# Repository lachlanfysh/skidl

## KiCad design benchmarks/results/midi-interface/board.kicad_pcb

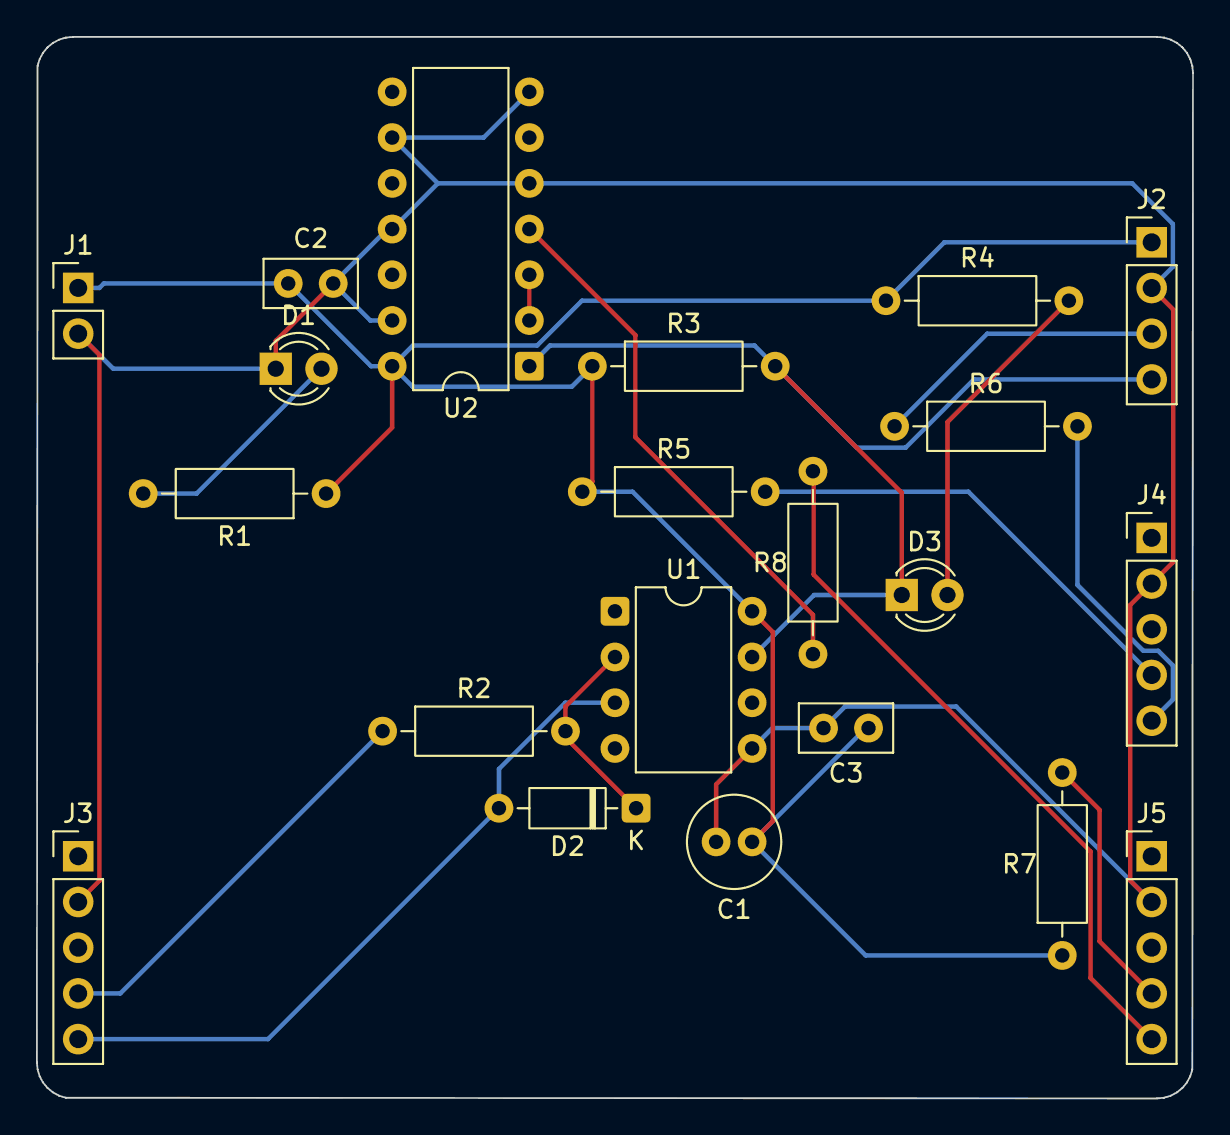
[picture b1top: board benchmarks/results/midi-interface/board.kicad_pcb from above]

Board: 2 copper layers, 64.2 x 59.0 mm, 21 parts (0 on the bottom side), 15 nets.

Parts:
C1: 10uF; C_Radial_D5.0mm_H11.0mm_P2.00mm
C2, C3: 100nF; C_Disc_D5.0mm_W2.5mm_P2.50mm
D1: GREEN; LED_D3.0mm
D2: 1N4148; D_DO-35_SOD27_P7.62mm_Horizontal
D3: YELLOW; LED_D3.0mm
J1: 5V PWR; PinHeader_1x02_P2.54mm_Vertical
J2: MCU HDR; PinHeader_1x04_P2.54mm_Vertical
J3: MIDI IN; PinHeader_1x05_P2.54mm_Vertical
J4: MIDI OUT; PinHeader_1x05_P2.54mm_Vertical
J5: MIDI THRU; PinHeader_1x05_P2.54mm_Vertical
R1, R4: 470; R_Axial_DIN0207_L6.3mm_D2.5mm_P10.16mm_Horizontal
R2, R5, R6, R7, R8: 220; R_Axial_DIN0207_L6.3mm_D2.5mm_P10.16mm_Horizontal
R3: 4.7k; R_Axial_DIN0207_L6.3mm_D2.5mm_P10.16mm_Horizontal
U1: 6N138; DIP-8_W7.62mm
U2: 74HC14; DIP-14_W7.62mm

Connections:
GND: C1.2, C2.2, C3.2, D1.1, J1.2, J2.2, J3.2, J4.2, J5.2, U1.5, U2.5, U2.7, U2.9, U2.11, U2.13
MIDI_IN_RAW: D3.1, J2.4, R3.2, U1.7, U2.1
MIDI_OUT_TX: J2.3, R6.1
MIDI_THRU_BUF: R8.1, U2.4
MID_INV: U2.2, U2.3
unnamed: D1.2, R1.2
unnamed: J3.4, R2.1
unnamed: D3.2, R4.2
unnamed: J4.4, R5.2
unnamed: J4.5, R6.2
unnamed: J5.4, R7.2
unnamed: J5.5, R8.2
OPTO_A: D2.1, R2.2, U1.2
OPTO_C: D2.2, J3.5, U1.3
VCC: C1.1, C2.1, C3.1, J1.1, J2.1, R1.1, R3.1, R4.1, R5.1, R7.1, U1.8, U2.14

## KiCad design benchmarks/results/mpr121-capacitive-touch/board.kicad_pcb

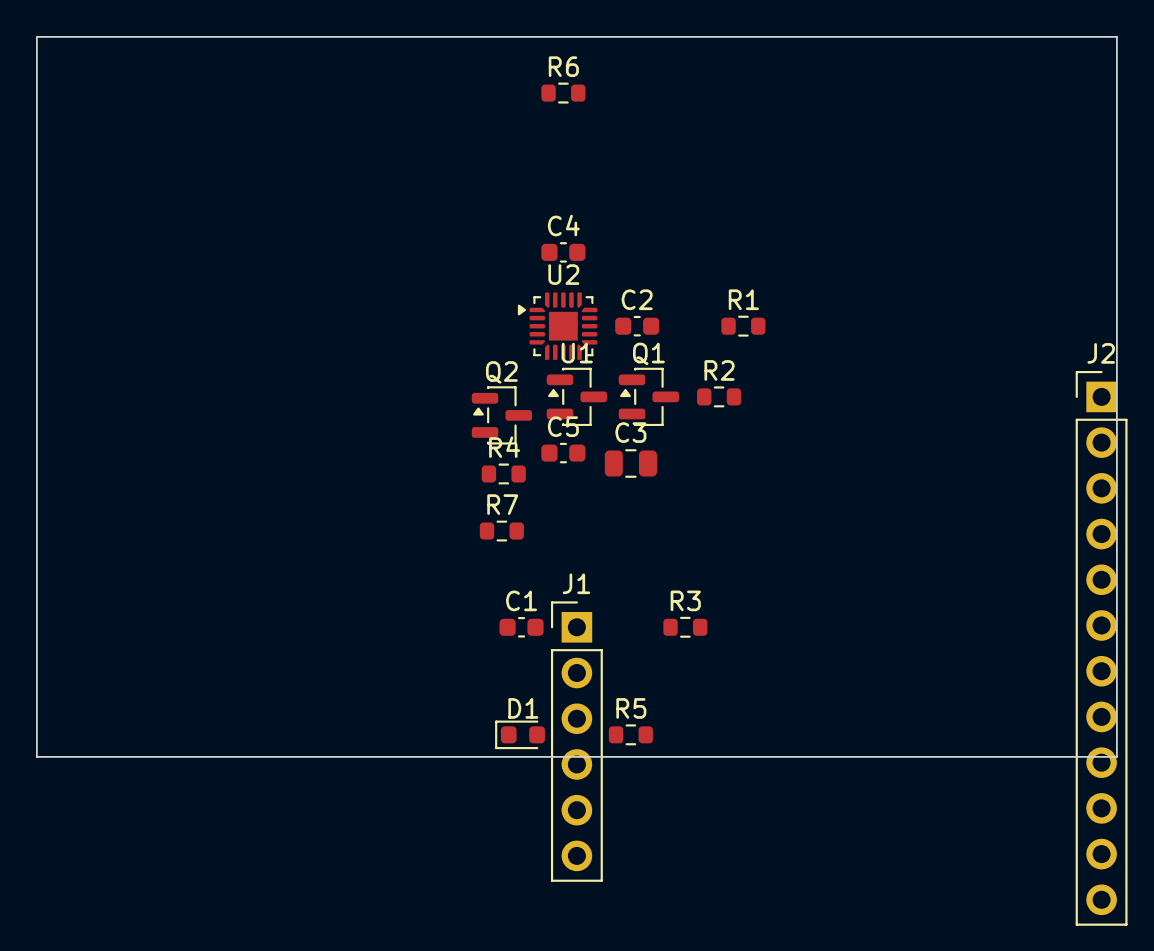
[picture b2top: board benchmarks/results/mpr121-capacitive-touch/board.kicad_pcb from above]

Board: 2 copper layers, 60.0 x 40.0 mm, 19 parts (0 on the bottom side), 23 nets, no tracks yet.

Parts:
C1, C2: 1uF; C_0603_1608Metric
C3: 10uF; C_0805_2012Metric
C4: 100nF; C_0603_1608Metric
C5: 10nF; C_0603_1608Metric
D1: RED; LED_0603_1608Metric
J1: HOST; PinHeader_1x06_P2.54mm_Vertical
J2: ELECTRODES; PinHeader_1x12_P2.54mm_Vertical
Q1, Q2: BSS138; SOT-23
R1: 0R; R_0603_1608Metric
R2, R3, R4, R5: 10K; R_0603_1608Metric
R6: 100K; R_0603_1608Metric
R7: 1K; R_0603_1608Metric
U1: MCP1700-3.3V; SOT-23
U2: MPR121QR2; QFN-20-1EP_3x3mm_P0.45mm_EP1.6x1.6mm

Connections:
+3V3: C2.1, C3.1, C4.1, Q1.1, Q2.1, R2.1, R4.1, R6.1, R7.1, U1.2, U2.19
ELE0: J2.1, U2.1
ELE1: J2.2, U2.2
ELE2: J2.3, U2.3
ELE3: J2.4, U2.4
ELE4: J2.5, U2.5
ELE5: J2.6, U2.6
ELE6: J2.7, U2.7
ELE7: J2.8, U2.11
ELE8: J2.9, U2.12
ELE9: J2.10, U2.13
ELE10: J2.11, U2.14
ELE11: J2.12, U2.15
GND: C1.2, C2.2, C3.2, C4.2, C5.2, J1.2, R1.2, U1.1, U2.8, U2.21
IRQ: D1.2, R6.2, U2.16
unnamed: C5.1, U2.10
unnamed: R1.1, U2.9
unnamed: D1.1, R7.2
SCL: J1.4, Q2.3, R5.2
SCL_3V3: Q2.2, R4.2, U2.18
SDA: J1.3, Q1.3, R3.2
SDA_3V3: Q1.2, R2.2, U2.17
VIN: C1.1, J1.1, U1.3

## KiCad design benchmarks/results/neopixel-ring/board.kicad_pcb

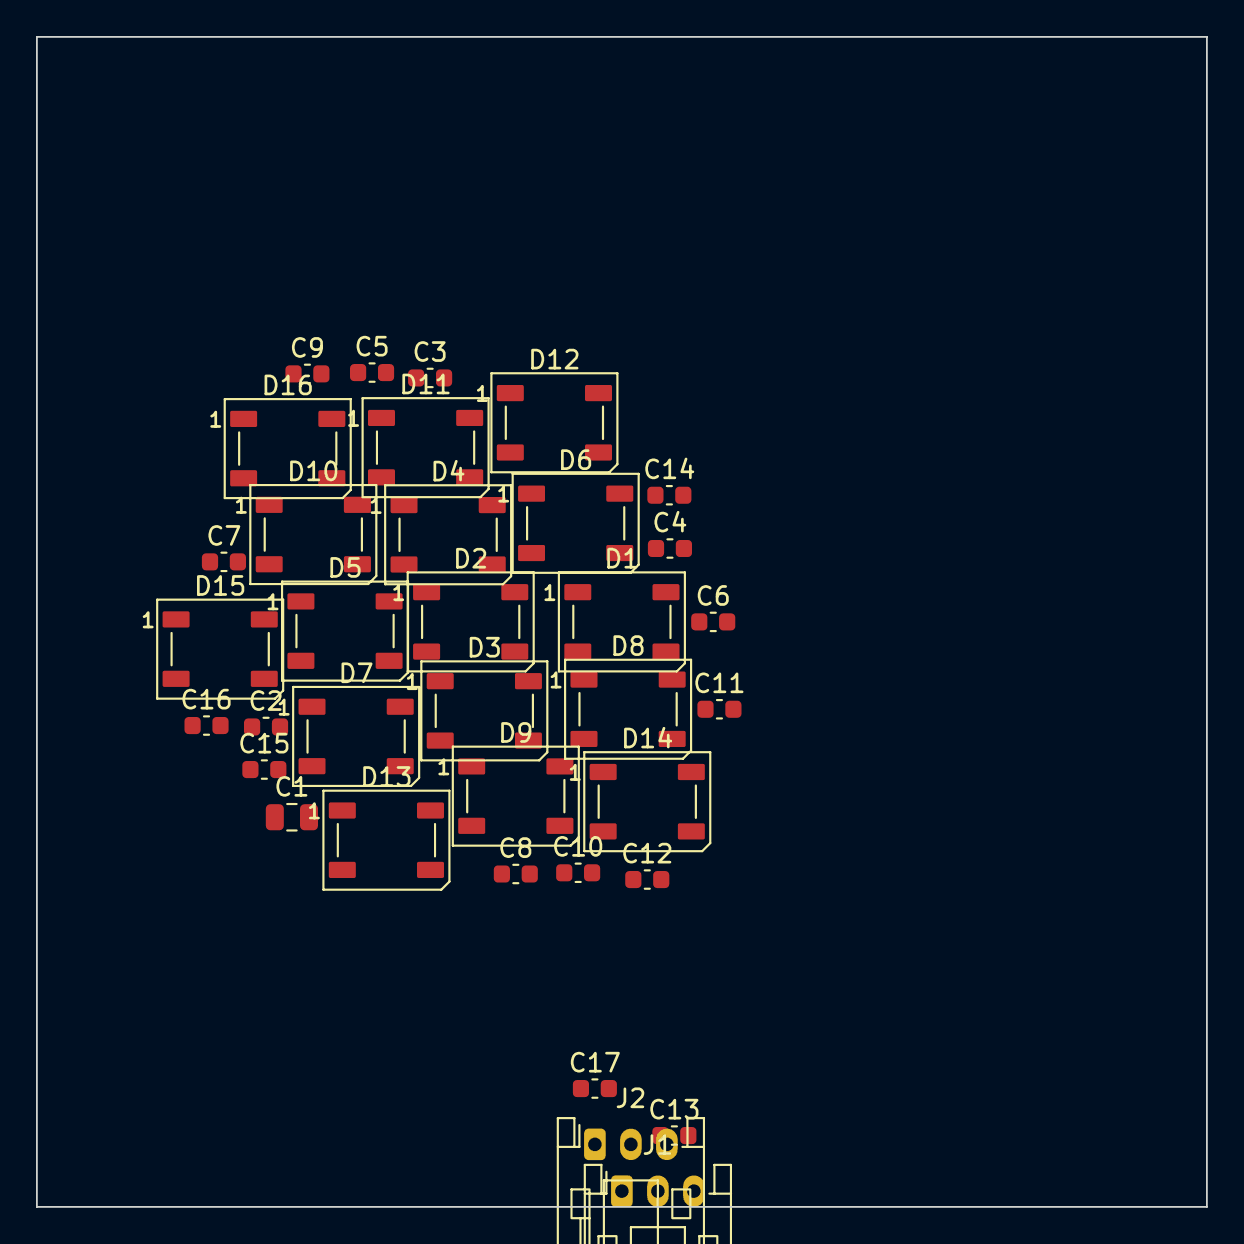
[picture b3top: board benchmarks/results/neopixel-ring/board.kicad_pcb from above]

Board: 2 copper layers, 65.0 x 65.0 mm, 35 parts (0 on the bottom side), 19 nets, no tracks yet.

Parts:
C1: 100uF; C_0805_2012Metric
C2, C3, C4, C5, C6, C7, C8, C9, C10, C11, C12, C13, C14, C15, C16, C17: 100nF; C_0603_1608Metric
D1, D2, D3, D4, D5, D6, D7, D8, D9, D10, D11, D12, D13, D14, D15, D16: WS2812B; LED_WS2812B_PLCC4_5.0x5.0mm_P3.2mm
J1: NeoPixel_In; JST_PH_S3B-PH-K_1x03_P2.00mm_Horizontal
J2: NeoPixel_Out; JST_PH_S3B-PH-K_1x03_P2.00mm_Horizontal

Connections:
+5V: C1.1, C2.1, C3.1, C4.1, C5.1, C6.1, C7.1, C8.1, C9.1, C10.1, C11.1, C12.1, C13.1, C14.1, C15.1, C16.1, C17.1, D1.1, D2.1, D3.1, D4.1, D5.1, D6.1, D7.1, D8.1, D9.1, D10.1, D11.1, D12.1, D13.1, D14.1, D15.1, D16.1, J1.1, J2.1
D1_D2: D1.2, D2.4
D2_D3: D2.2, D3.4
D3_D4: D3.2, D4.4
D4_D5: D4.2, D5.4
D5_D6: D5.2, D6.4
D6_D7: D6.2, D7.4
D7_D8: D7.2, D8.4
D8_D9: D8.2, D9.4
D9_D10: D9.2, D10.4
D10_D11: D10.2, D11.4
D11_D12: D11.2, D12.4
D12_D13: D12.2, D13.4
D13_D14: D13.2, D14.4
D14_D15: D14.2, D15.4
D15_D16: D15.2, D16.4
DIN: D1.4, J1.2
DOUT: D16.2, J2.2
GND: C1.2, C2.2, C3.2, C4.2, C5.2, C6.2, C7.2, C8.2, C9.2, C10.2, C11.2, C12.2, C13.2, C14.2, C15.2, C16.2, C17.2, D1.3, D2.3, D3.3, D4.3, D5.3, D6.3, D7.3, D8.3, D9.3, D10.3, D11.3, D12.3, D13.3, D14.3, D15.3, D16.3, J1.3, J2.3

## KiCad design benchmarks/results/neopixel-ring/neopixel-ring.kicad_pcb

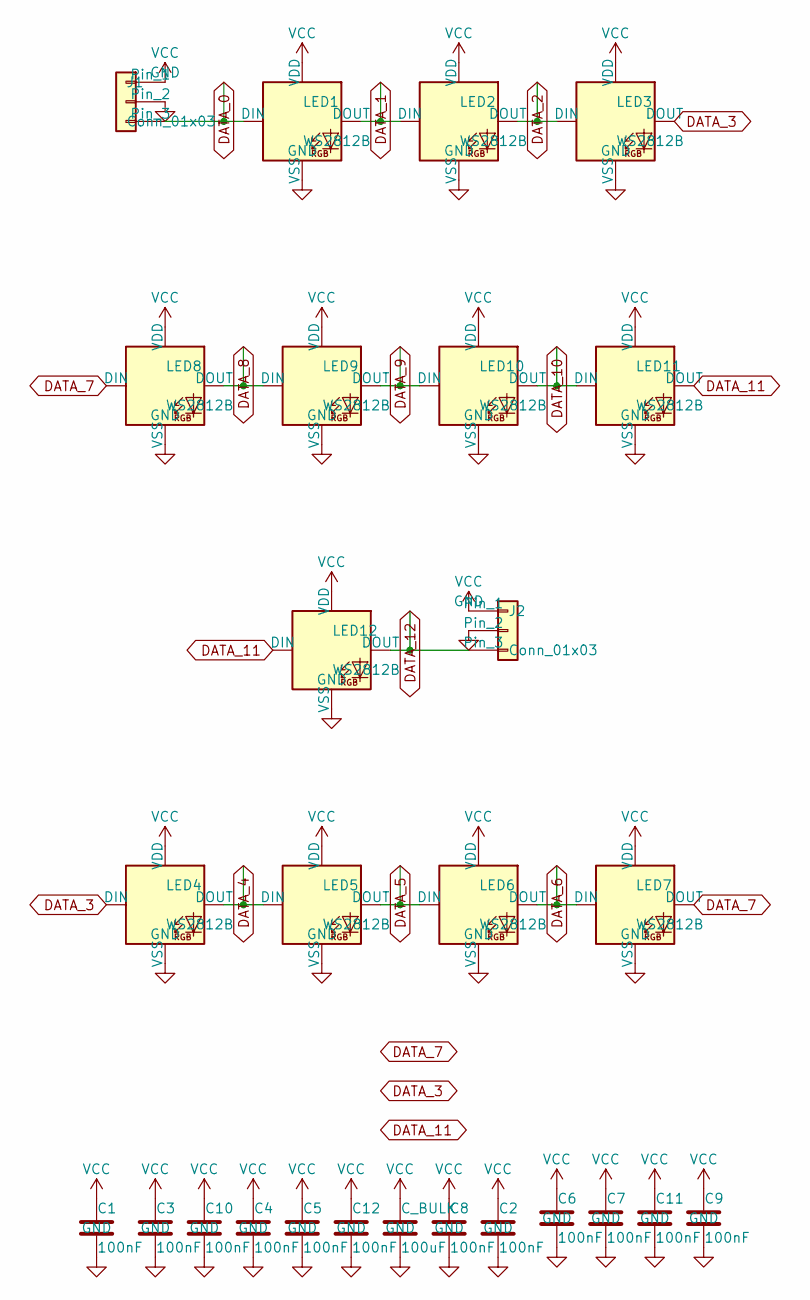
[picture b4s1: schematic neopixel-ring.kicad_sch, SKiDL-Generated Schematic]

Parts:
C1, C2, C3, C4, C5, C6, C7, C8, C9, C10, C11, C12: 100nF; C_0402_1005Metric
C_BULK: 100uF; C_1210_3225Metric
J1, J2: Conn_01x03; PinHeader_1x03_P2.54mm_Vertical
LED1, LED2, LED3, LED4, LED5, LED6, LED7, LED8, LED9, LED10, LED11, LED12: WS2812B; LED_WS2812B_PLCC4_5.0x5.0mm_P3.2mm

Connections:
DATA_0: J1.3, LED1.4 (DIN)
DATA_1: LED1.2 (DOUT), LED2.4 (DIN)
DATA_2: LED2.2 (DOUT), LED3.4 (DIN)
DATA_3: LED3.2 (DOUT), LED4.4 (DIN)
DATA_4: LED4.2 (DOUT), LED5.4 (DIN)
DATA_5: LED5.2 (DOUT), LED6.4 (DIN)
DATA_6: LED6.2 (DOUT), LED7.4 (DIN)
DATA_7: LED7.2 (DOUT), LED8.4 (DIN)
DATA_8: LED8.2 (DOUT), LED9.4 (DIN)
DATA_9: LED9.2 (DOUT), LED10.4 (DIN)
DATA_10: LED10.2 (DOUT), LED11.4 (DIN)
DATA_11: LED11.2 (DOUT), LED12.4 (DIN)
DATA_12: J2.3, LED12.2 (DOUT)
GND: C1.2, C2.2, C3.2, C4.2, C5.2, C6.2, C7.2, C8.2, C9.2, C10.2, C11.2, C12.2, C_BULK.2, J1.2, J2.2, LED1.3 (VSS), LED2.3 (VSS), LED3.3 (VSS), LED4.3 (VSS), LED5.3 (VSS), LED6.3 (VSS), LED7.3 (VSS), LED8.3 (VSS), LED9.3 (VSS), LED10.3 (VSS), LED11.3 (VSS), LED12.3 (VSS)
VCC: C1.1, C2.1, C3.1, C4.1, C5.1, C6.1, C7.1, C8.1, C9.1, C10.1, C11.1, C12.1, C_BULK.1, J1.1, J2.1, LED1.1 (VDD), LED2.1 (VDD), LED3.1 (VDD), LED4.1 (VDD), LED5.1 (VDD), LED6.1 (VDD), LED7.1 (VDD), LED8.1 (VDD), LED9.1 (VDD), LED10.1 (VDD), LED11.1 (VDD), LED12.1 (VDD)

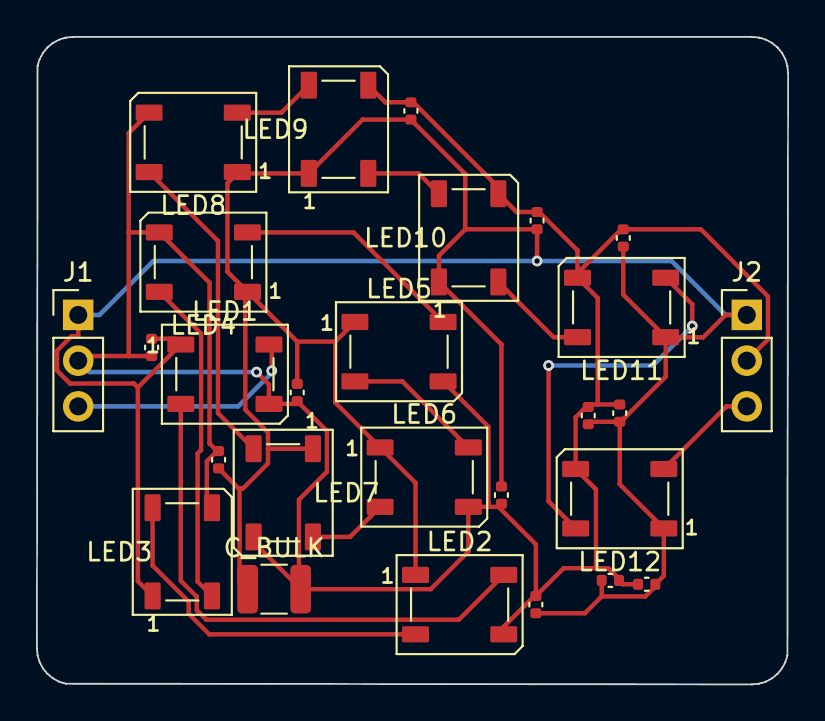
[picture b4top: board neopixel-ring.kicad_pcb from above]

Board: 2 copper layers, 41.7 x 36.0 mm, 27 parts (0 on the bottom side), 15 nets.

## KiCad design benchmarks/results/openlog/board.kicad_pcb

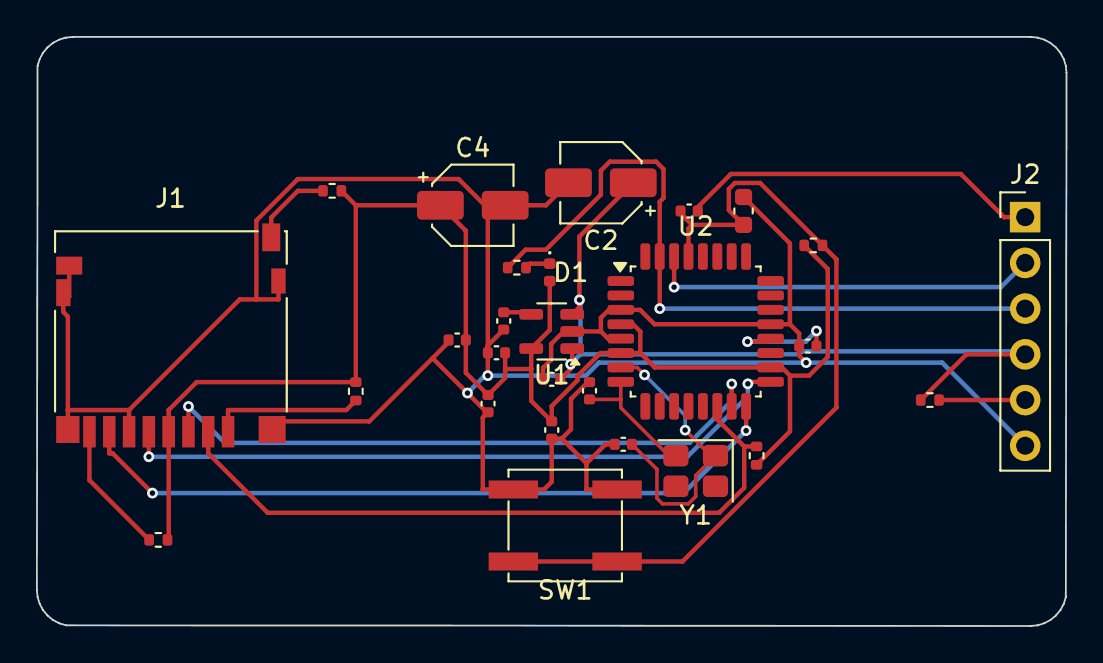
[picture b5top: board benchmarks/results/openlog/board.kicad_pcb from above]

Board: 2 copper layers, 57.2 x 32.7 mm, 27 parts (0 on the bottom side), 20 nets.

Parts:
C1, C3, C5, C6, C7, C8, C11, C12: 100nF; C_0402_1005Metric
C2, C4: 10uF; CP_Elec_4x5.4
C9, C10: 22pF; C_0402_1005Metric
C13: 100nF; C_0603_1608Metric
D1: STAT; LED_0402_1005Metric
J1: Micro_SD_Card_Det2; microSD_HC_Hirose_DM3D-SF
J2: FTDI_HEADER; PinHeader_1x06_P2.54mm_Vertical
R1, R2, R3, R4, R5, R6: 10K; R_0402_1005Metric
R7: 1K; R_0402_1005Metric
SW1: SW_Push; SW_SPST_EVPBF
U1: MIC5205-3.3YM5; SOT-23-5
U2: ATmega328P-A; TQFP-32_7x7mm_P0.8mm
Y1: 16MHz; Crystal_SMD_3225-4Pin_3.2x2.5mm

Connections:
3V3: C4.1, C5.1, C6.1, C7.1, C11.1, D1.2, J1.4, R1.1, R2.1, R3.1, R4.1, R5.1, U1.5, U2.4, U2.6, U2.18
CTS: J2.5, R6.2
DTR_RESET: C12.1, J2.1
GND: C1.2, C2.2, C3.2, C4.2, C5.2, C6.2, C7.2, C8.2, C9.2, C10.2, C11.2, C13.2, J1.6, J1.9, J1.11, J2.6, SW1.2, U1.2, U2.3, U2.5, U2.21
LDO_BP: C1.1, U1.4
unnamed: C8.1, U2.20
unnamed: J1.8, R2.2
unnamed: J1.1, R3.2
unnamed: D1.1, R7.1
RESET: C12.2, C13.1, R1.2, SW1.1, U2.29
SD_CS: J1.2, R4.2, U2.14
SD_DET: J1.10, R5.2
SPI_MISO: J1.7, U2.16
SPI_MOSI: J1.3, U2.15
SPI_SCK: J1.5, U2.17
UART_RX: J2.2, U2.30
UART_TX: J2.3, R7.2, U2.31
VCC: C2.1, C3.1, J2.4, R6.1, U1.1, U1.3
XTAL1: C9.1, U2.7, Y1.1
XTAL2: C10.1, U2.8, Y1.2

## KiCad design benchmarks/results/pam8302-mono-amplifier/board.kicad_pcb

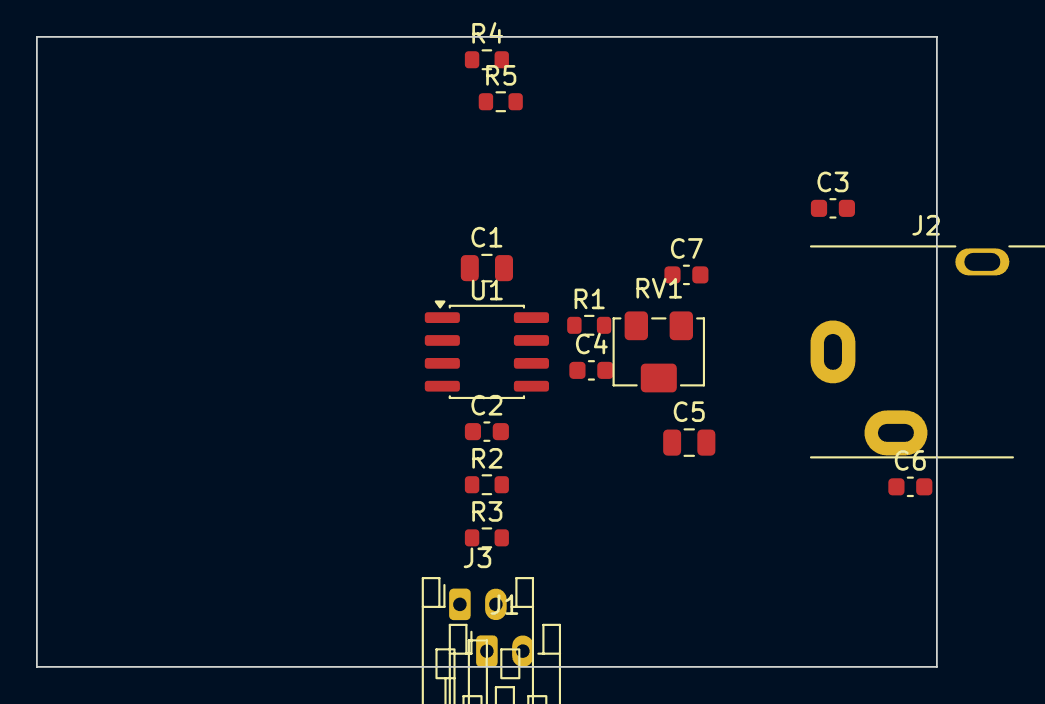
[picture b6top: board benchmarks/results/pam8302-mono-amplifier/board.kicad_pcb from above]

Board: 2 copper layers, 50.0 x 35.0 mm, 17 parts (0 on the bottom side), 12 nets, no tracks yet.

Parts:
C1: 100uF; C_0805_2012Metric
C2, C4, C6, C7: 100nF; C_0603_1608Metric
C3: 1uF; C_0603_1608Metric
C5: 10uF; C_0805_2012Metric
J1: PWR_IN; JST_PH_S2B-PH-K_1x02_P2.00mm_Horizontal
J2: 3.5mm_IN; Jack_3.5mm_CUI_SJ1-3513N_Horizontal
J3: SPEAKER; JST_PH_S2B-PH-K_1x02_P2.00mm_Horizontal
R1, R2: 1K; R_0603_1608Metric
R3: 100K; R_0603_1608Metric
R4, R5: 10R; R_0603_1608Metric
RV1: 10K; Potentiometer_Bourns_3214W_Vertical
U1: PAM8302AAD; SOIC-8_3.9x4.9mm_P1.27mm

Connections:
GND: C1.2, C2.2, C4.2, C5.2, C6.2, C7.2, J1.2, J2.S, R2.2, RV1.3, U1.7
IN_N: R2.1, U1.4
IN_P: R1.2, U1.3
unnamed: C3.1, J2.T
unnamed: C3.2, RV1.1
unnamed: R1.1, RV1.2
unnamed: R3.2, U1.1
unnamed: C6.1, R4.2
unnamed: C7.1, R5.2
OUT_N: J3.2, R5.1, U1.8
OUT_P: J3.1, R4.1, U1.5
VDD: C1.1, C2.1, C4.1, C5.1, J1.1, R3.1, U1.6

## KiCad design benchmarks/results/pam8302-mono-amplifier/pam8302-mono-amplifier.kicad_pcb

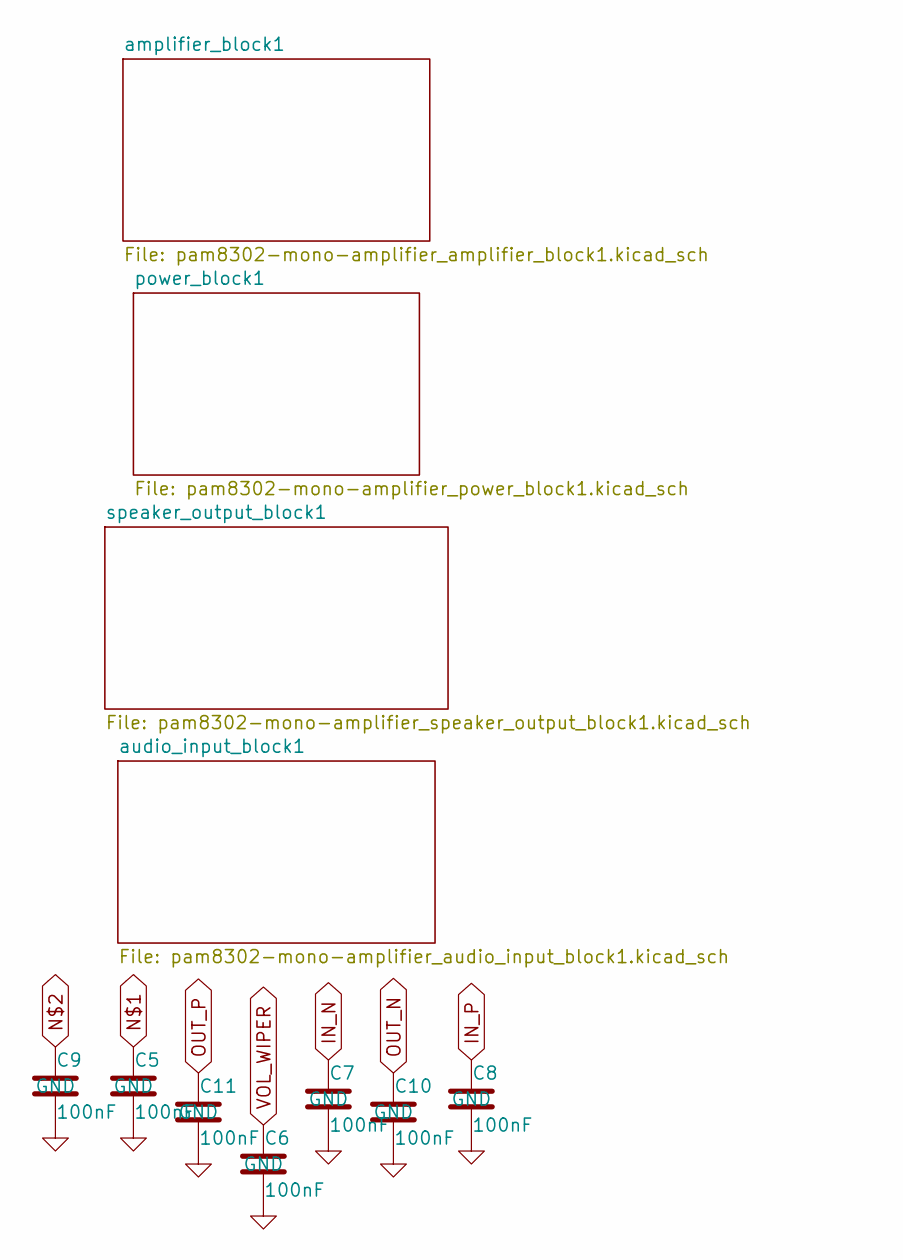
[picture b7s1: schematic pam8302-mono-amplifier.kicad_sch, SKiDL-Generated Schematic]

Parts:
C5, C6, C7, C8, C9, C10, C11: 100nF; C_0603_1608Metric

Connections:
GND: C5.2, C6.2, C7.2, C8.2, C9.2, C10.2, C11.2; also elsewhere on the board
IN_N: C7.1; also elsewhere on the board
IN_P: C8.1; also elsewhere on the board
unnamed 4: C5.1; also elsewhere on the board
unnamed 5: C9.1; also elsewhere on the board
OUT_N: C10.1; also elsewhere on the board
OUT_P: C11.1; also elsewhere on the board
VOL_WIPER: C6.1; also elsewhere on the board

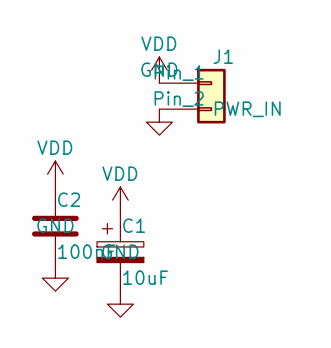
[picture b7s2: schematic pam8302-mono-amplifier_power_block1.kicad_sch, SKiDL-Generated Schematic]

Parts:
C1: 10uF; C_0805_2012Metric
C2: 100nF; C_0603_1608Metric
J1: PWR_IN; PinHeader_1x02_P2.54mm_Vertical

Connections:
GND: C1.2, C2.2, J1.2; also elsewhere on the board
VDD: C1.1, C2.1, J1.1; also elsewhere on the board

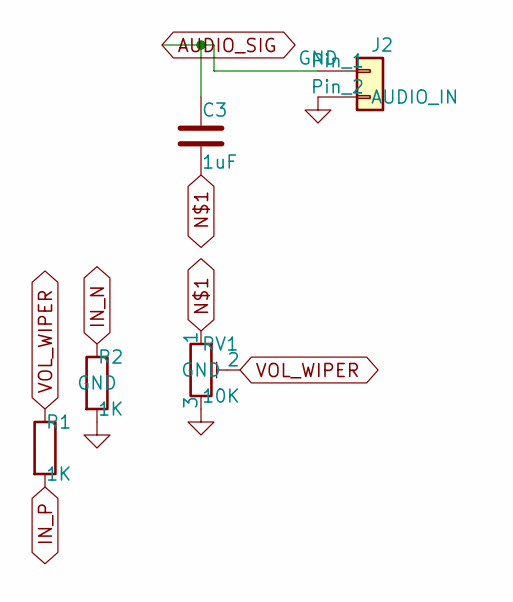
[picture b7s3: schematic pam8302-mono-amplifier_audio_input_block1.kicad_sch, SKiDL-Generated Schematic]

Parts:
C3: 1uF; C_0603_1608Metric
J2: AUDIO_IN; PinHeader_1x02_P2.54mm_Vertical
R1, R2: 1K; R_0603_1608Metric
RV1: 10K; Potentiometer_Bourns_3296W_Vertical

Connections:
AUDIO_SIG: C3.1, J2.1
GND: J2.2, R2.2, RV1.3; also elsewhere on the board
IN_N: R2.1; also elsewhere on the board
IN_P: R1.2; also elsewhere on the board
unnamed 4: C3.2, RV1.1; also elsewhere on the board
VOL_WIPER: R1.1, RV1.2; also elsewhere on the board

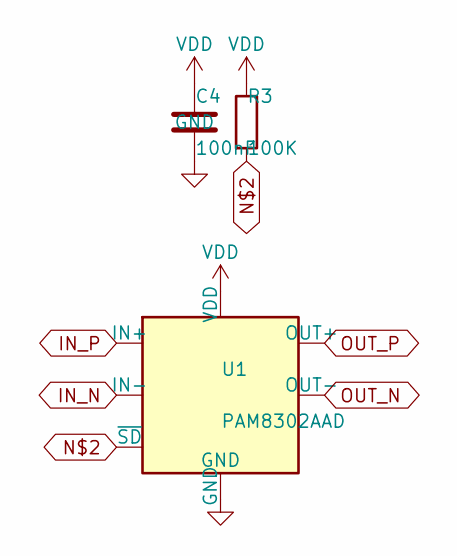
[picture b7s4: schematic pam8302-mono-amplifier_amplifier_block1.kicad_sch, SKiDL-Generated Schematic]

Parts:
C4: 100nF; C_0603_1608Metric
R3: 100K; R_0603_1608Metric
U1: PAM8302AAD; SOIC-8_3.9x4.9mm_P1.27mm

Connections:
GND: C4.2, U1.7 (GND); also elsewhere on the board
IN_N: U1.4 (IN-); also elsewhere on the board
IN_P: U1.3 (IN+); also elsewhere on the board
unnamed 5: R3.2, U1.1 (~SD); also elsewhere on the board
OUT_N: U1.8 (OUT-); also elsewhere on the board
OUT_P: U1.5 (OUT+); also elsewhere on the board
VDD: C4.1, R3.1, U1.6 (VDD); also elsewhere on the board

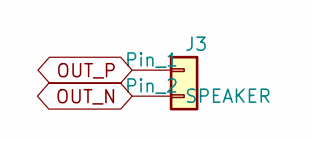
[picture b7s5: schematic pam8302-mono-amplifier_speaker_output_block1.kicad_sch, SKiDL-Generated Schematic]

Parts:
J3: SPEAKER; PinHeader_1x02_P2.54mm_Vertical

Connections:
OUT_N: J3.2; also elsewhere on the board
OUT_P: J3.1; also elsewhere on the board

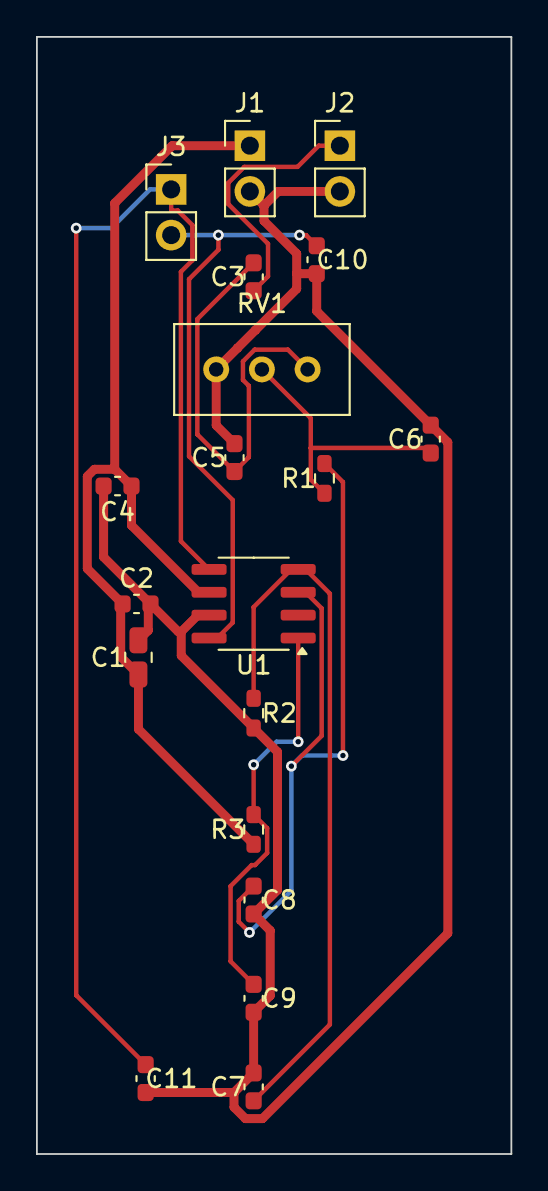
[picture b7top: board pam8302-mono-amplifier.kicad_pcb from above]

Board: 2 copper layers, 26.4 x 62.1 mm, 19 parts (0 on the bottom side), 10 nets.

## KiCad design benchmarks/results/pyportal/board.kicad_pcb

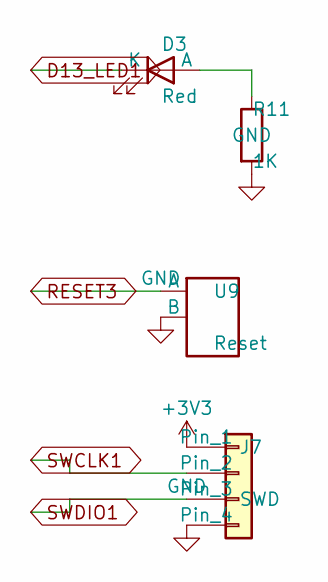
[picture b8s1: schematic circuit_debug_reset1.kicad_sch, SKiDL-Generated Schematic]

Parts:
D3: Red; LED_0603_1608Metric
J7: SWD; PinHeader_1x04_P1.27mm_Vertical
R11: 1K; R_0402_1005Metric
U9: Reset; SW_SPST_PTS645

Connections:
+3V3: J7.1; also elsewhere on the board
D13_LED1: D3.1 (K)
GND: J7.4, R11.2, U9.2 (B); also elsewhere on the board
unnamed: D3.2 (A), R11.1
RESET3: U9.1 (A)
SWCLK1: J7.2
SWDIO1: J7.3

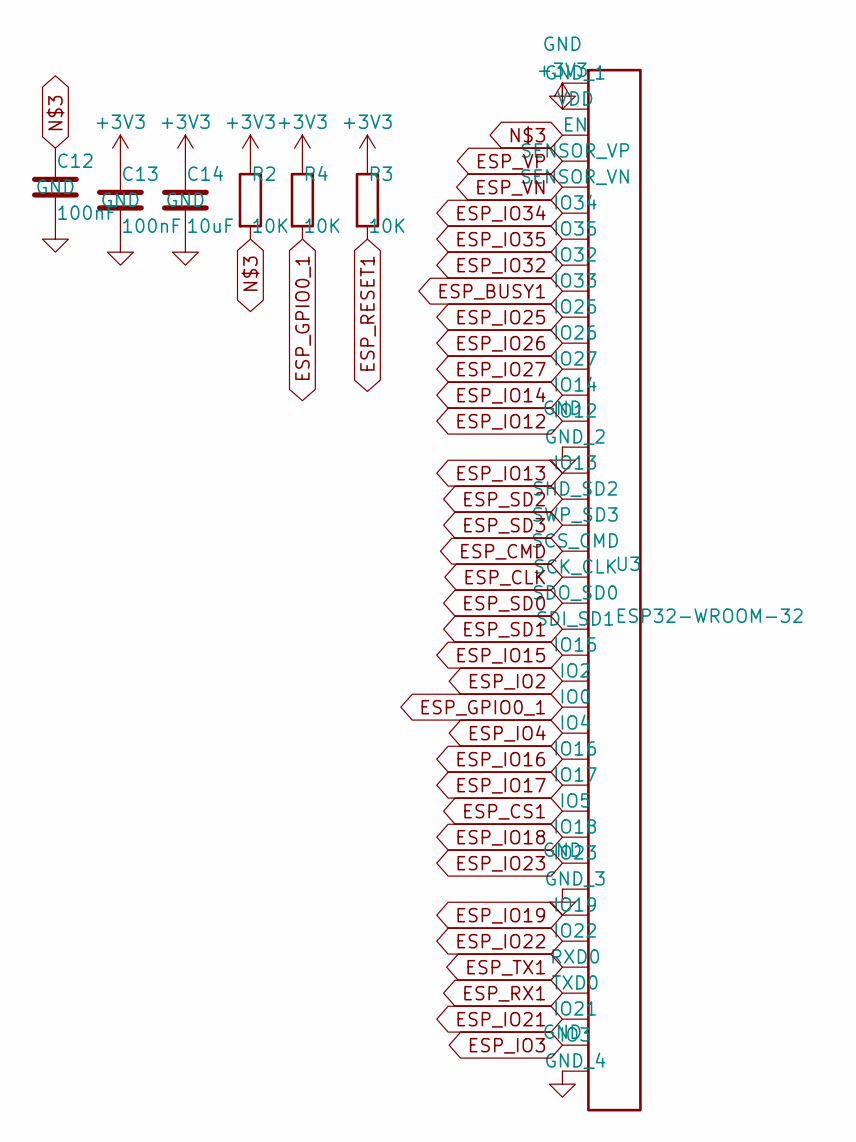
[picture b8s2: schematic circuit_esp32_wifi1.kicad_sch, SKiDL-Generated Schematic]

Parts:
C12: 100nF; C_0402_1005Metric
C13: 100nF; C_0603_1608Metric
C14: 10uF; C_0805_2012Metric
R2, R3, R4: 10K; R_0402_1005Metric
U3: ESP32-WROOM-32

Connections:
+3V3: C13.1, C14.1, R2.1, R3.1, R4.1, U3.2 (VDD); also elsewhere on the board
ESP_BUSY1: U3.9 (IO33)
ESP_CLK: U3.20 (SCK_CLK)
ESP_CMD: U3.19 (SCS_CMD)
ESP_CS1: U3.29 (IO5)
ESP_GPIO0_1: R4.2, U3.25 (IO0)
ESP_IO2: U3.24 (IO2)
ESP_IO3: U3.38 (IO3)
ESP_IO4: U3.26 (IO4)
ESP_IO12: U3.14 (IO12)
ESP_IO13: U3.16 (IO13)
ESP_IO14: U3.13 (IO14)
ESP_IO15: U3.23 (IO15)
ESP_IO16: U3.27 (IO16)
ESP_IO17: U3.28 (IO17)
ESP_IO18: U3.30 (IO18)
ESP_IO19: U3.33 (IO19)
ESP_IO21: U3.37 (IO21)
ESP_IO22: U3.34 (IO22)
ESP_IO23: U3.31 (IO23)
ESP_IO25: U3.10 (IO25)
ESP_IO26: U3.11 (IO26)
ESP_IO27: U3.12 (IO27)
ESP_IO32: U3.8 (IO32)
ESP_IO34: U3.6 (IO34)
ESP_IO35: U3.7 (IO35)
ESP_RESET1: R3.2
ESP_RX1: U3.36 (TXD0)
ESP_SD0: U3.21 (SDO_SD0)
ESP_SD1: U3.22 (SDI_SD1)
ESP_SD2: U3.17 (SHD_SD2)
ESP_SD3: U3.18 (SWP_SD3)
ESP_TX1: U3.35 (RXD0)
ESP_VN: U3.5 (SENSOR_VN)
ESP_VP: U3.4 (SENSOR_VP)
GND: C12.2, C13.2, C14.2, U3.1 (GND_1), U3.15 (GND_2), U3.32 (GND_3), U3.39 (GND_4); also elsewhere on the board
unnamed: C12.1, R2.2, U3.3 (EN)

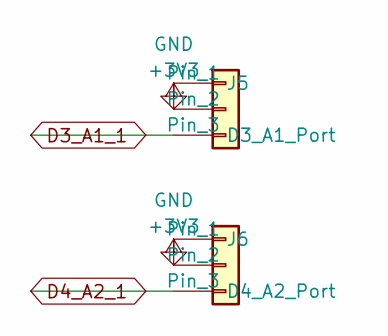
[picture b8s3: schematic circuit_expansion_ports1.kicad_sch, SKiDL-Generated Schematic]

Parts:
J5: D3_A1_Port; JST_PH_S3B-PH-K_1x03_P2.00mm_Horizontal
J6: D4_A2_Port; JST_PH_S3B-PH-K_1x03_P2.00mm_Horizontal

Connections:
+3V3: J5.2, J6.2; also elsewhere on the board
D3_A1_1: J5.3
D4_A2_1: J6.3
GND: J5.1, J6.1; also elsewhere on the board

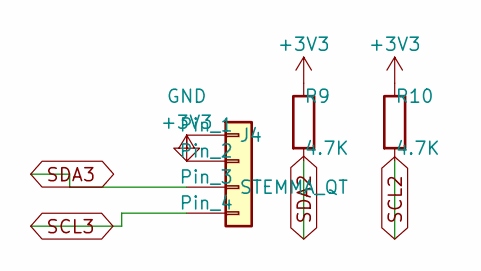
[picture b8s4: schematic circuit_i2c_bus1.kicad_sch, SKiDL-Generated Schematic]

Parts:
J4: STEMMA_QT; JST_SH_SM04B-SRSS-TB_1x04-1MP_P1.00mm_Horizontal
R9, R10: 4.7K; R_0402_1005Metric

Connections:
+3V3: J4.2, R9.1, R10.1; also elsewhere on the board
GND: J4.1; also elsewhere on the board
SCL2: R10.2
SCL3: J4.4
SDA2: R9.2
SDA3: J4.3

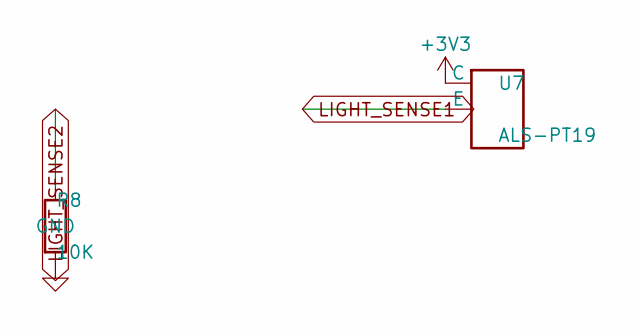
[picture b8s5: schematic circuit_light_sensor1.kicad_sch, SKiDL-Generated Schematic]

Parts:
R8: 10K; R_0603_1608Metric
U7: ALS-PT19; LED_0805_2012Metric

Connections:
+3V3: U7.1 (C); also elsewhere on the board
GND: R8.2; also elsewhere on the board
LIGHT_SENSE1: U7.2 (E)
LIGHT_SENSE2: R8.1

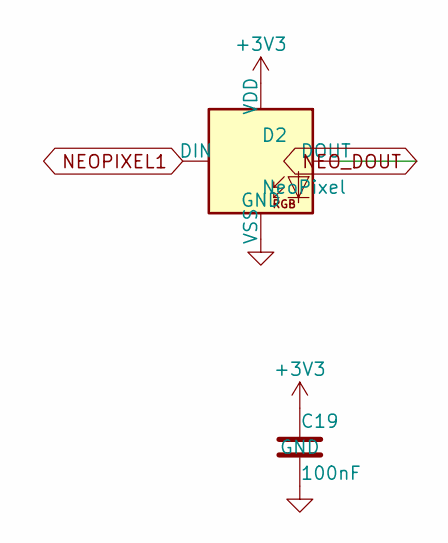
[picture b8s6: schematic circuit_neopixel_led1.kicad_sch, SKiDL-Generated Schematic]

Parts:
C19: 100nF; C_0603_1608Metric
D2: NeoPixel; LED_WS2812B_PLCC4_5.0x5.0mm_P3.2mm

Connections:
+3V3: C19.1, D2.3 (VDD); also elsewhere on the board
GND: C19.2, D2.1 (VSS); also elsewhere on the board
NEOPIXEL1: D2.2 (DIN)
NEO_DOUT: D2.4 (DOUT)

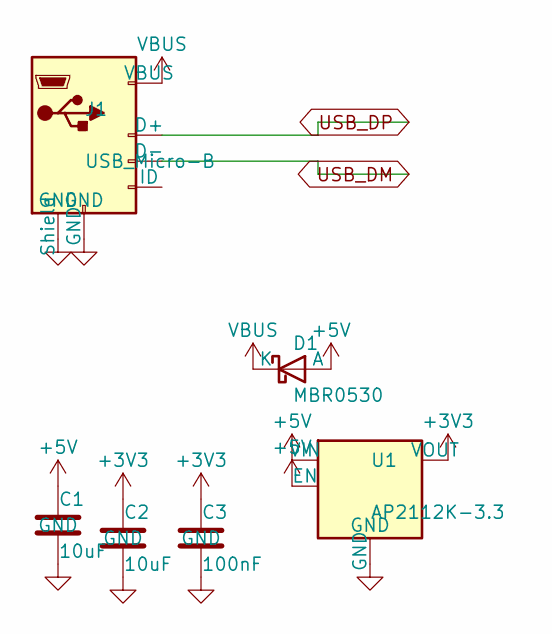
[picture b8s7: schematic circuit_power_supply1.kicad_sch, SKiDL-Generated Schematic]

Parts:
C1, C2: 10uF; C_0805_2012Metric
C3: 100nF; C_0603_1608Metric
D1: MBR0530; D_SOD-123
J1: USB_Micro-B; USB_Micro-B_Molex_47346-0001
U1: AP2112K-3.3; SOT-23-5

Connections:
+3V3: C2.1, C3.1, U1.5 (VOUT); also elsewhere on the board
+5V: C1.1, D1.2 (A), U1.1 (VIN), U1.3 (EN)
GND: C1.2, C2.2, C3.2, J1.5 (GND), J1.6 (Shield), U1.2 (GND); also elsewhere on the board
USB_DM: J1.2 (D-)
USB_DP: J1.3 (D+)
VBUS: D1.1 (K), J1.1 (VBUS)
